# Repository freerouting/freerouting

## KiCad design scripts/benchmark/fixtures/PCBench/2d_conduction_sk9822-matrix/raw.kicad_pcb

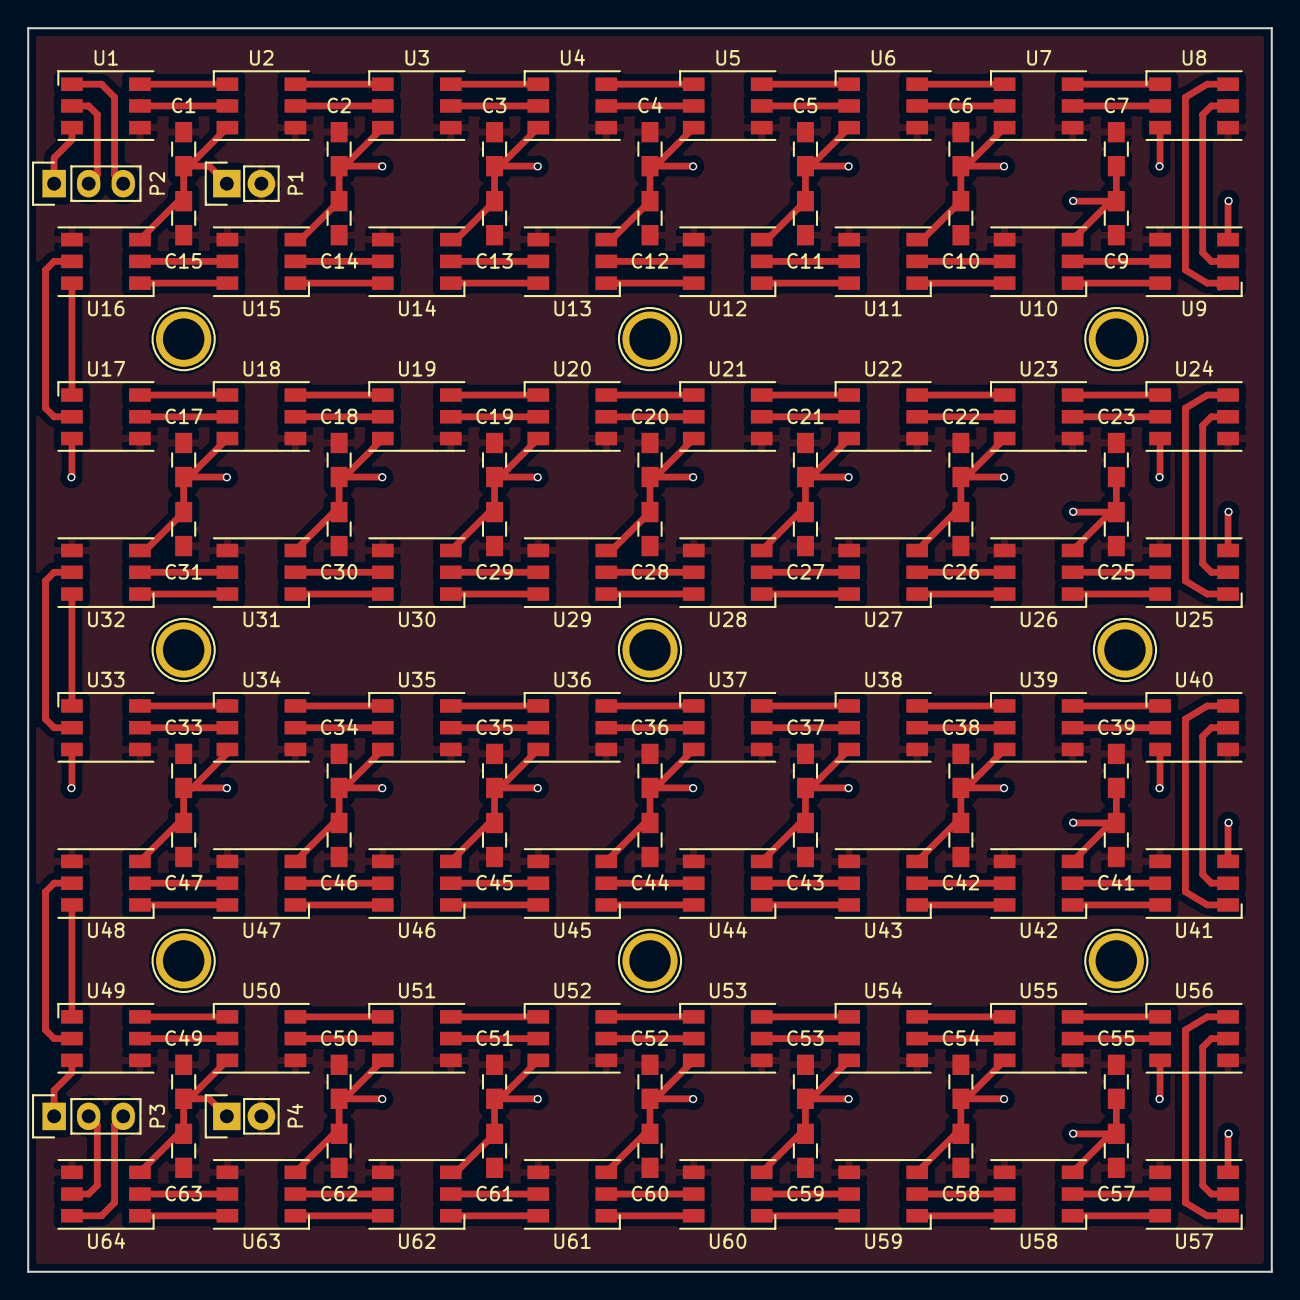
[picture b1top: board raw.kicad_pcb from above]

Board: 2 copper layers, 91.4 x 91.4 mm, 133 parts (0 on the bottom side), 132 nets.

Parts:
C1, C2, C3, C4, C5, C6, C7, C9, C10, C11, C12, C13, C14, C15, C17, C18, C19, C20, C21, C22, C23, C25, C26, C27, C28, C29, C30, C31, C33, C34, C35, C36, C37, C38, C39, C41, C42, C43, C44, C45, C46, C47, C49, C50, C51, C52, C53, C54, C55, C57, C58, C59, C60, C61, C62, C63: 0.1uF; C_0805_HandSoldering
H1, H2, H3, H4, H5, H6, H7, H8, H9: 1pin
P1: PWR IN; Pin_Header_Straight_1x02
P2: DATA IN; Pin_Header_Straight_1x03
P3: DATA OUT; Pin_Header_Straight_1x03
P4: PWR OUT; Pin_Header_Straight_1x02
U1, U2, U3, U4, U5, U6, U7, U8, U9, U10, U11, U12, U13, U14, U15, U16, U17, U18, U19, U20, U21, U22, U23, U24, U25, U26, U27, U28, U29, U30, U31, U32, U33, U34, U35, U36, U37, U38, U39, U40, U41, U42, U43, U44, U45, U46, U47, U48, U49, U50, U51, U52, U53, U54, U55, U56, U57, U58, U59, U60, U61, U62, U63, U64: SK9822; LED_WS2812-PLCC6

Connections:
+5V: C1.2, C2.2, C3.2, C4.2, C5.2, C6.2, C7.2, C9.2, C10.2, C11.2, C12.2, C13.2, C14.2, C15.2, C17.2, C18.2, C19.2, C20.2, C21.2, C22.2, C23.2, C25.2, C26.2, C27.2, C28.2, C29.2, C30.2, C31.2, C33.2, C34.2, C35.2, C36.2, C37.2, C38.2, C39.2, C41.2, C42.2, C43.2, C44.2, C45.2, C46.2, C47.2, C49.2, C50.2, C51.2, C52.2, C53.2, C54.2, C55.2, C57.2, C58.2, C59.2, C60.2, C61.2, C62.2, C63.2, P1.2, P4.2, U1.4, U2.4, U3.4, U4.4, U5.4, U6.4, U7.4, U8.4, U9.4, U10.4, U11.4, U12.4, U13.4, U14.4, U15.4, U16.4, U17.4, U18.4, U19.4, U20.4, U21.4, U22.4, U23.4, U24.4, U25.4, U26.4, U27.4, U28.4, U29.4, U30.4, U31.4, U32.4, U33.4, U34.4, U35.4, U36.4, U37.4, U38.4, U39.4, U40.4, U41.4, U42.4, U43.4, U44.4, U45.4, U46.4, U47.4, U48.4, U49.4, U50.4, U51.4, U52.4, U53.4, U54.4, U55.4, U56.4, U57.4, U58.4, U59.4, U60.4, U61.4, U62.4, U63.4, U64.4
/CKI: P2.2, U1.2
/CKO: P3.2, U64.5
/CKO8: U8.5, U9.2
/CKO16: U16.5, U17.2
/CKO24: U24.5, U25.2
/CKO32: U32.5, U33.2
/CKO40: U40.5, U41.2
/CKO48: U48.5, U49.2
/CKO56: U56.5, U57.2
/SDI: P2.3, U1.1
/SDO: P3.3, U64.6
/SDO8: U8.6, U9.1
/SDO16: U16.6, U17.1
/SDO24: U24.6, U25.1
/SDO32: U32.6, U33.1
/SDO40: U40.6, U41.1
/SDO48: U48.6, U49.1
/SDO56: U56.6, U57.1
GND: C1.1, C2.1, C3.1, C4.1, C5.1, C6.1, C7.1, C9.1, C10.1, C11.1, C12.1, C13.1, C14.1, C15.1, C17.1, C18.1, C19.1, C20.1, C21.1, C22.1, C23.1, C25.1, C26.1, C27.1, C28.1, C29.1, C30.1, C31.1, C33.1, C34.1, C35.1, C36.1, C37.1, C38.1, C39.1, C41.1, C42.1, C43.1, C44.1, C45.1, C46.1, C47.1, C49.1, C50.1, C51.1, C52.1, C53.1, C54.1, C55.1, C57.1, C58.1, C59.1, C60.1, C61.1, C62.1, C63.1, P1.1, P2.1, P3.1, P4.1, U1.3, U2.3, U3.3, U4.3, U5.3, U6.3, U7.3, U8.3, U9.3, U10.3, U11.3, U12.3, U13.3, U14.3, U15.3, U16.3, U17.3, U18.3, U19.3, U20.3, U21.3, U22.3, U23.3, U24.3, U25.3, U26.3, U27.3, U28.3, U29.3, U30.3, U31.3, U32.3, U33.3, U34.3, U35.3, U36.3, U37.3, U38.3, U39.3, U40.3, U41.3, U42.3, U43.3, U44.3, U45.3, U46.3, U47.3, U48.3, U49.3, U50.3, U51.3, U52.3, U53.3, U54.3, U55.3, U56.3, U57.3, U58.3, U59.3, U60.3, U61.3, U62.3, U63.3, U64.3
unnamed: U1.5, U2.2
unnamed: U1.6, U2.1
unnamed: U2.5, U3.2
unnamed: U2.6, U3.1
unnamed: U3.5, U4.2
unnamed: U3.6, U4.1
unnamed: U4.5, U5.2
unnamed: U4.6, U5.1
unnamed: U5.5, U6.2
unnamed: U5.6, U6.1
unnamed: U6.5, U7.2
unnamed: U6.6, U7.1
unnamed: U7.5, U8.2
unnamed: U7.6, U8.1
unnamed: U9.6, U10.1
unnamed: U9.5, U10.2
unnamed: U10.5, U11.2
unnamed: U10.6, U11.1
unnamed: U11.5, U12.2
unnamed: U11.6, U12.1
unnamed: U12.5, U13.2
unnamed: U12.6, U13.1
unnamed: U13.5, U14.2
unnamed: U13.6, U14.1
unnamed: U14.5, U15.2
unnamed: U14.6, U15.1
unnamed: U15.5, U16.2
unnamed: U15.6, U16.1
unnamed: U17.5, U18.2
unnamed: U17.6, U18.1
unnamed: U18.5, U19.2
unnamed: U18.6, U19.1
unnamed: U19.5, U20.2
unnamed: U19.6, U20.1
unnamed: U20.5, U21.2
unnamed: U20.6, U21.1
unnamed: U21.5, U22.2
unnamed: U21.6, U22.1
unnamed: U22.5, U23.2
unnamed: U22.6, U23.1
unnamed: U23.5, U24.2
unnamed: U23.6, U24.1
unnamed: U25.5, U26.2
unnamed: U25.6, U26.1
unnamed: U26.5, U27.2
unnamed: U26.6, U27.1
unnamed: U27.5, U28.2
unnamed: U27.6, U28.1
unnamed: U28.5, U29.2
unnamed: U28.6, U29.1
unnamed: U29.5, U30.2
unnamed: U29.6, U30.1
unnamed: U30.5, U31.2
unnamed: U30.6, U31.1
unnamed: U31.5, U32.2
unnamed: U31.6, U32.1
unnamed: U33.5, U34.2
unnamed: U33.6, U34.1
unnamed: U34.5, U35.2
unnamed: U34.6, U35.1
unnamed: U35.5, U36.2
unnamed: U35.6, U36.1
unnamed: U36.5, U37.2
unnamed: U36.6, U37.1
unnamed: U37.5, U38.2
unnamed: U37.6, U38.1
unnamed: U38.5, U39.2
unnamed: U38.6, U39.1
unnamed: U39.5, U40.2
unnamed: U39.6, U40.1
unnamed: U41.5, U42.2
unnamed: U41.6, U42.1
unnamed: U42.5, U43.2
unnamed: U42.6, U43.1
unnamed: U43.5, U44.2
unnamed: U43.6, U44.1
unnamed: U44.5, U45.2
unnamed: U44.6, U45.1
unnamed: U45.5, U46.2
unnamed: U45.6, U46.1
unnamed: U46.5, U47.2
unnamed: U46.6, U47.1
unnamed: U47.5, U48.2
unnamed: U47.6, U48.1
unnamed: U49.5, U50.2
unnamed: U49.6, U50.1
unnamed: U50.5, U51.2
unnamed: U50.6, U51.1
unnamed: U51.5, U52.2
unnamed: U51.6, U52.1
unnamed: U52.5, U53.2
unnamed: U52.6, U53.1
unnamed: U53.5, U54.2
unnamed: U53.6, U54.1
unnamed: U54.5, U55.2
unnamed: U54.6, U55.1
unnamed: U55.5, U56.2
unnamed: U55.6, U56.1
unnamed: U57.5, U58.2
unnamed: U57.6, U58.1
unnamed: U58.5, U59.2
unnamed: U58.6, U59.1
unnamed: U59.5, U60.2
unnamed: U59.6, U60.1
unnamed: U60.5, U61.2
unnamed: U60.6, U61.1
unnamed: U61.5, U62.2
unnamed: U61.6, U62.1
unnamed: U62.5, U63.2
unnamed: U62.6, U63.1
unnamed: U63.5, U64.2
unnamed: U63.6, U64.1

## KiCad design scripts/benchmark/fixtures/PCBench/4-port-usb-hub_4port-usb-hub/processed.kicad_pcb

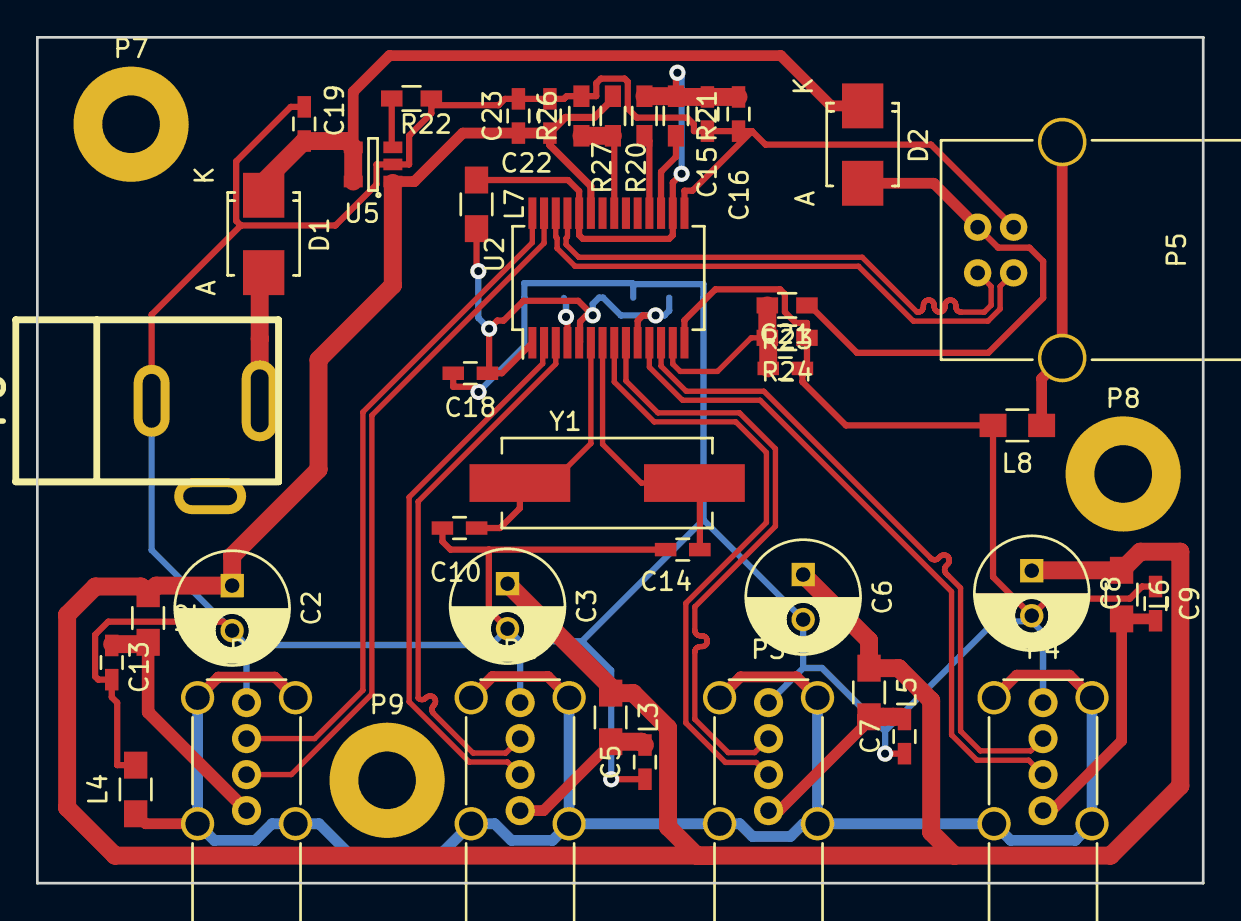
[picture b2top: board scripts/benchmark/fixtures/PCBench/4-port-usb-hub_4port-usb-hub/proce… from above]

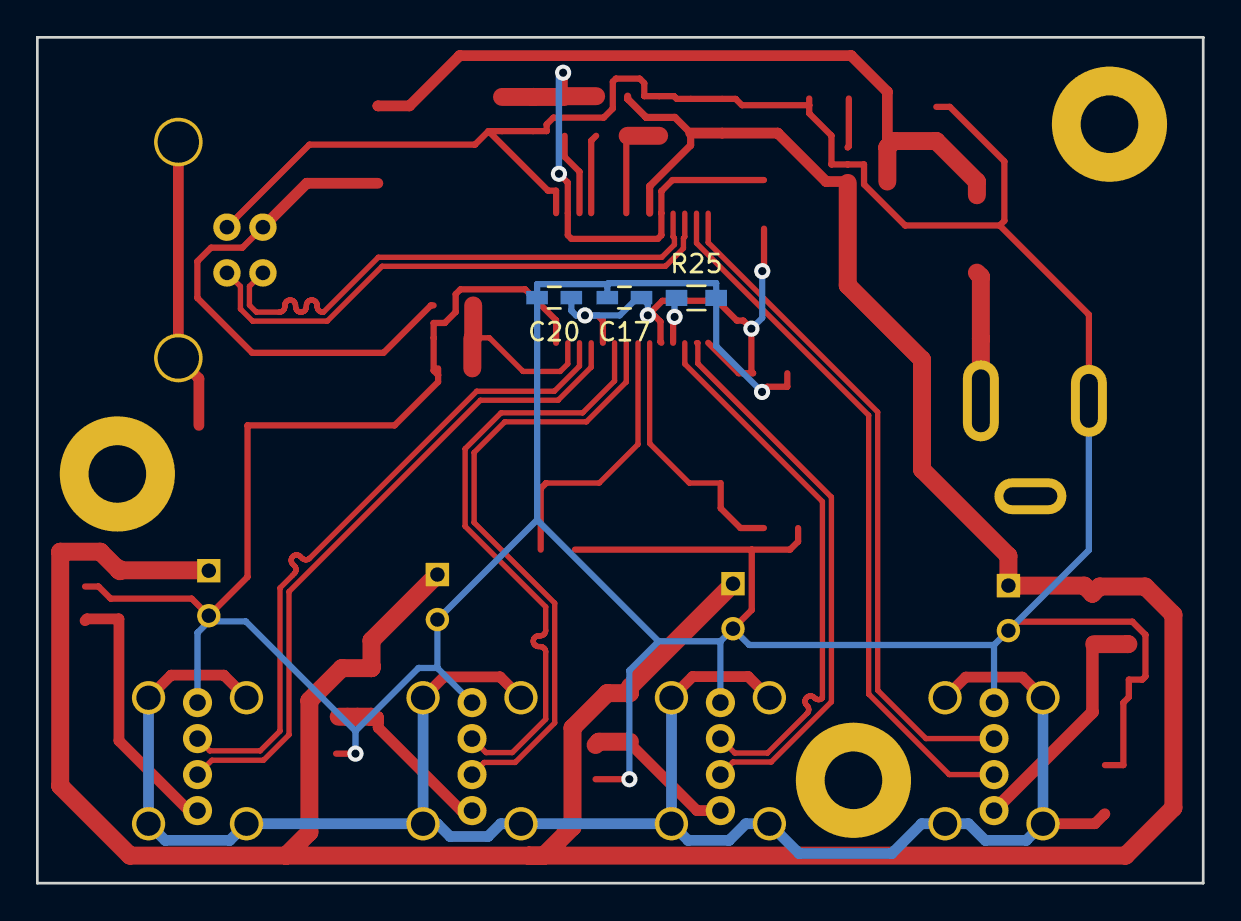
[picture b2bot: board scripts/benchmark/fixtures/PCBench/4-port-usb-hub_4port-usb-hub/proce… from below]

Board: 2 copper layers, 64.8 x 47.0 mm, 48 parts (3 on the bottom side), 31 nets.

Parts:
C2, C3, C6, C8: 100uF/16V/LOWESR/105C; C_Radial_D6.3_L11.2_P2.5
C5, C7, C9, C13: 0.1uF; C_0603_HandSoldering
C10, C14: 33pF; C_0603_HandSoldering
C15, C17, C18, C20, C23: 100nF; C_0603_HandSoldering
C16, C19, C22: 10uF/6.3V; C_0603_HandSoldering
C21: 1uF; C_0603_HandSoldering
D1, D2: D; SMB_Standard
L2, L3, L4, L5, L6, L7: 600R/2A; R_0805_HandSoldering
L8: 600R/200mA; R_0805_HandSoldering
P1, P2, P3, P4: USB_A; USB_A_Vertical
P5: USB_B
P6: CONN_01X03; dc_socket
P7, P8, P9: CONN_01X01; MountingHole_3.2mm_M3_Pad
R20, R24: 47k; R_0603_HandSoldering
R21, R23, R26: 10k; R_0603_HandSoldering
R22: 4.7k/1%; R_0603_HandSoldering
R25: 680R/1%; R_0603_HandSoldering
R27: 5.1k; R_0603_HandSoldering
U2: GL850G; SSOP-28_5.3x10.2mm_Pitch0.65mm
U5: SY6280; SOT-23-5
Y1: 12Mhz; Crystal_HC49-SD_SMD

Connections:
/5V: C19.2, D1.1, D2.1, U5.4, U5.5
/5V-DP: C2.1, C3.1, C6.1, C8.1, C22.1, C23.1, L2.1, L3.1, L5.1, L6.1, R27.1, U2.23, U5.1
/5V-IN-USB: D2.2, P5.1, R23.1
/AVDD: C17.1, C18.1, C20.1, L7.2, U2.1, U2.5, U2.10
/V33: C15.1, C16.1, L7.1, R20.1, R21.1, U2.16, U2.24
D0+: P5.3, U2.26
D0-: P5.2, U2.25
D1+: P2.3, U2.28
D1-: P2.2, U2.27
D2+: P1.3, U2.3
D2-: P1.2, U2.2
D3+: P3.3, U2.9
D3-: P3.2, U2.8
D4+: P4.3, U2.12
D4-: P4.2, U2.11
GND: C2.2, C3.2, C5.1, C6.2, C7.1, C8.2, C9.1, C10.2, C13.1, C14.2, C15.2, C16.2, C17.2, C18.2, C19.1, C20.2, C21.2, C22.2, C23.2, L4.2, L8.2, P1.4, P2.4, P3.4, P4.4, P5.4, P6.2, R22.2, R24.1, R25.2, R26.2, U2.14, U2.15, U5.2
unnamed: C5.2, L3.2, P1.1
unnamed: C7.2, L5.2, P3.1
unnamed: C9.2, L6.2, P4.1
unnamed: C10.1, U2.6, Y1.1
unnamed: C13.2, L2.2, P2.1
unnamed: C14.1, U2.7, Y1.2
unnamed: C21.1, R23.2, R24.2, U2.13
unnamed: D1.2, P6.3
unnamed: L4.1, P1.5, P2.5, P3.5, P4.5
unnamed: L8.1, P5.5
unnamed: R20.2, U2.18
unnamed: R21.2, U2.17
unnamed: R22.1, U5.3
unnamed: R25.1, U2.4
unnamed: R26.1, R27.2, U2.21

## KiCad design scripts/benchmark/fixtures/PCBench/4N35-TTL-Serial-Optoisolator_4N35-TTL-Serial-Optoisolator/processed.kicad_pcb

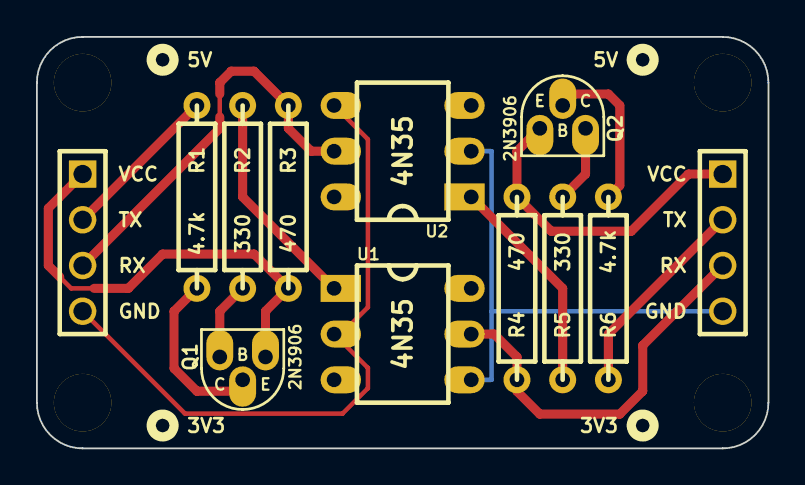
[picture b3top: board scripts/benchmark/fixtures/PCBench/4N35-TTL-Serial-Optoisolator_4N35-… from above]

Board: 2 copper layers, 40.6 x 22.9 mm, 16 parts (0 on the bottom side), 14 nets.

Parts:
H***: Val**; hole_M3_2
H***_2, H***_3, H***_4: Val**; hole_M3_2
P1, P2: CONN_4; PIN_ARRAY_4x1
Q1, Q2: 2N3906; TO-92_Q_EBC_059Bo_PL
R1, R6: 4.7k; R_AXIAL_0W25_059A_PL
R2, R5: 330; R_AXIAL_0W25_059A_PL
R3, R4: 470; R_AXIAL_0W25_059A_PL
U1, U2: 4N35; DIP6_PL

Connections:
GNDA: P1.4, U1.2, U2.4
GNDB: P2.4, U1.4, U2.2
unnamed: Q2.2, R6.2
unnamed: Q2.3, R5.2
unnamed: R5.1, U2.1
unnamed: Q1.3, R2.2
unnamed: Q1.2, R1.2
unnamed: R2.1, U1.1
RXA: P1.3, R3.1, U2.5
RXB: P2.3, R4.1, U1.5
TXA: P1.2, R1.1
TXB: P2.2, R6.1
VCCA: P1.1, Q1.1, R3.2
VCCB: P2.1, Q2.1, R4.2
